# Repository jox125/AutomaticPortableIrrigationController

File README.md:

# Automatic Portable Irrigation System

This automatic watering system was developed and manufactured as my final thesis in Mechatronics at the Võru County Vocational Education Center.
In this repository you find two main parts: 
1. Water distribution system hardware overview
2. Controller software

All parts are placed in a common housing to ensure easy installation and transportation of the system.

You can find additional information in my thesis in [here](/assets/Joel_Lepp_Thesis_est.docx)

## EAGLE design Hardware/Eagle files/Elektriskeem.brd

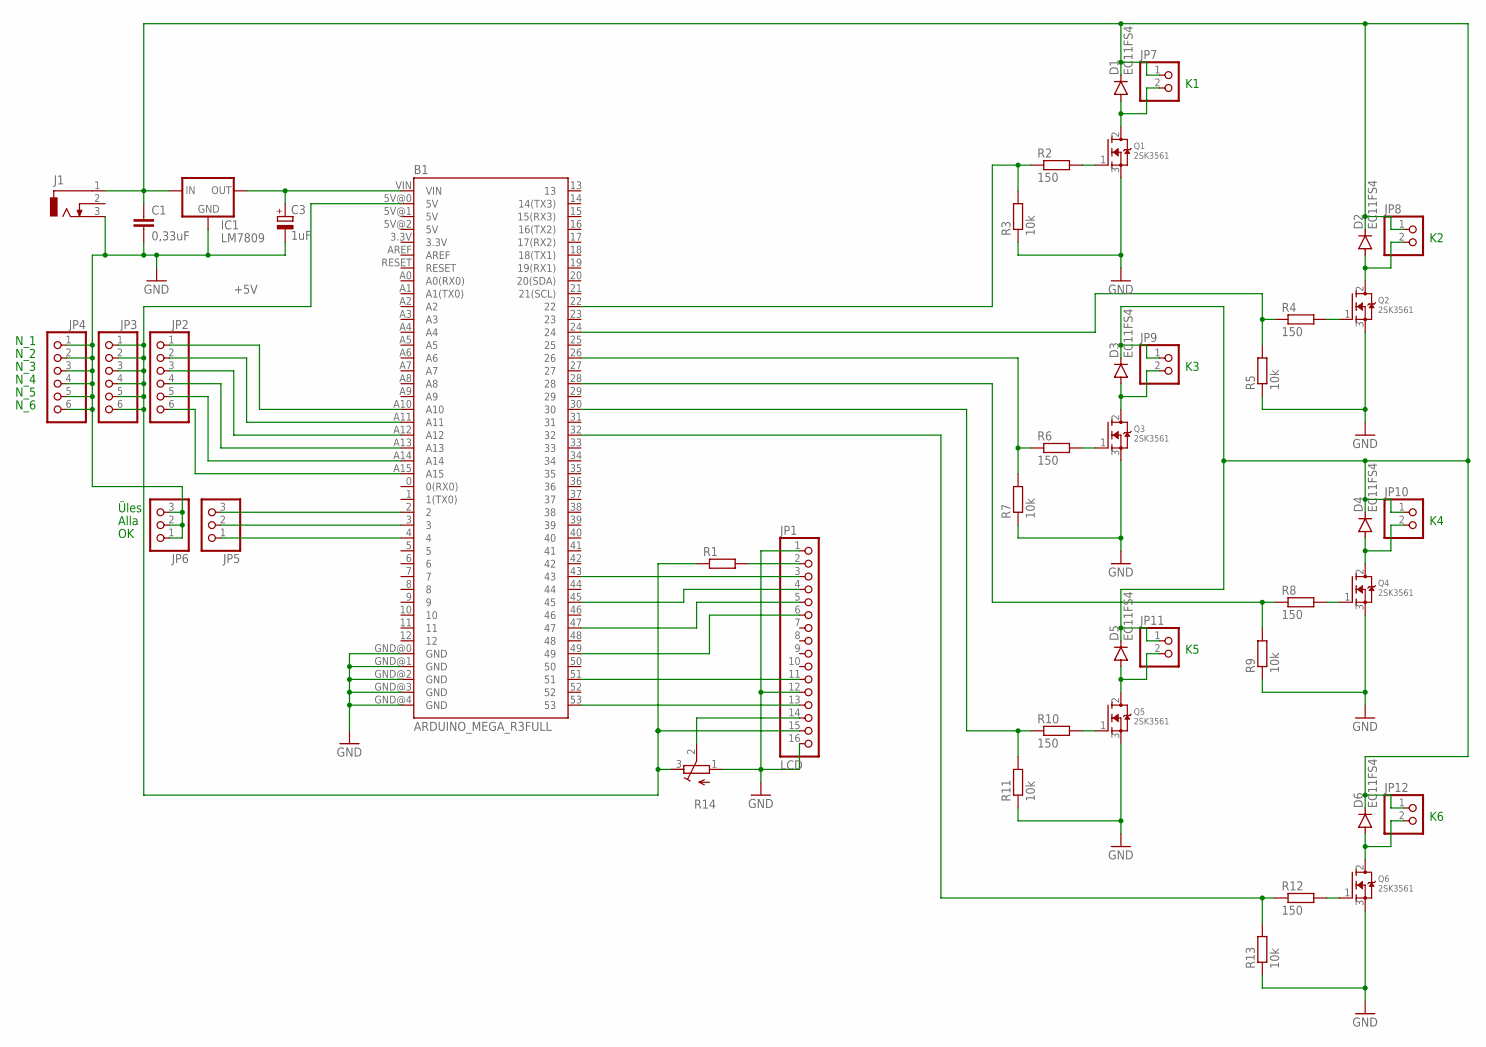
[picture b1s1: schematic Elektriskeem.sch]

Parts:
B1: ARDUINO_MEGA_R3FULL; ARDUINO_MEGA
C1: 0,33uF; C102-043X133
C3: 1uF; E2,5-6
D1, D2, D3, D4, D5, D6: EC11FS4; DO214AA
IC1: LM7809; 78XXS
J1: DCJ0303
JP1: LCD; 1X16
JP2, JP3, JP4: PINHD-1X6; 1X06
JP5, JP6: PINHD-1X3; 1X03
JP7, JP8, JP9, JP10, JP11, JP12: PINHD-1X2; 1X02
Q1, Q2, Q3, Q4, Q5, Q6: 2SK3561; TO220V
R1: R-EU_0207/12; 0207/12
R2, R4, R6, R8, R10, R12: 150; 0207/12
R3, R5, R7, R9, R11, R13: 10k; 0207/12
R14: R-TRIMM3339P; RTRIM3339P

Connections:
+5V: B1.5V@0 (5V), JP1.15, JP3.1, JP3.2, JP3.3, JP3.4, JP3.5, JP3.6, R1.1, R14.3 (E)
GND: B1.GND@0 (GND), B1.GND@1 (GND), B1.GND@2 (GND), B1.GND@3 (GND), B1.GND@4 (GND), C1.2, C3.-, IC1.GND, J1.3, JP1.1, JP1.12, JP1.16, JP4.1, JP4.2, JP4.3, JP4.4, JP4.5, JP4.6, JP6.1, JP6.2, JP6.3, Q1.3 (S), Q2.3 (S), Q3.3 (S), Q4.3 (S), Q5.3 (S), Q6.3 (S), R3.1, R5.1, R7.1, R9.1, R11.1, R13.1, R14.1 (A)
unnamed: C1.1, D1.C, D2.C, D3.C, D4.C, D5.C, D6.C, IC1.IN, J1.1, JP7.1, JP8.1, JP9.1, JP10.1, JP11.1, JP12.1
unnamed: B1.2, JP5.3
unnamed: B1.VIN, C3.+, IC1.OUT
unnamed: B1.A15, JP2.6
unnamed: B1.26, R6.1, R7.2
unnamed: B1.A14, JP2.5
unnamed: B1.A13, JP2.4
unnamed: B1.A12, JP2.3
unnamed: B1.A11, JP2.2
unnamed: B1.A10, JP2.1
unnamed: B1.43, JP1.3
unnamed: B1.53, JP1.13
unnamed: JP1.2, R1.2
unnamed: JP1.14, R14.2 (S)
unnamed: B1.51, JP1.11
unnamed: B1.45, JP1.4
unnamed: B1.47, JP1.5
unnamed: B1.49, JP1.6
unnamed: B1.3, JP5.2
unnamed: B1.4, JP5.1
unnamed: Q1.1 (G), R2.2
unnamed: D1.A, JP7.2, Q1.2 (D)
unnamed: B1.22, R2.1, R3.2
unnamed: D3.A, JP9.2, Q3.2 (D)
unnamed: Q3.1 (G), R6.2
unnamed: D5.A, JP11.2, Q5.2 (D)
unnamed: Q5.1 (G), R10.2
unnamed: B1.30, R10.1, R11.2
unnamed: D2.A, JP8.2, Q2.2 (D)
unnamed: Q2.1 (G), R4.2
unnamed: B1.24, R4.1, R5.2
unnamed: D4.A, JP10.2, Q4.2 (D)
unnamed: Q4.1 (G), R8.2
unnamed: B1.28, R8.1, R9.2
unnamed: D6.A, JP12.2, Q6.2 (D)
unnamed: Q6.1 (G), R12.2
unnamed: B1.32, R12.1, R13.2

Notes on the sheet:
Üles
Alla
N_1
N_2
N_3
N_4
N_5
N_6

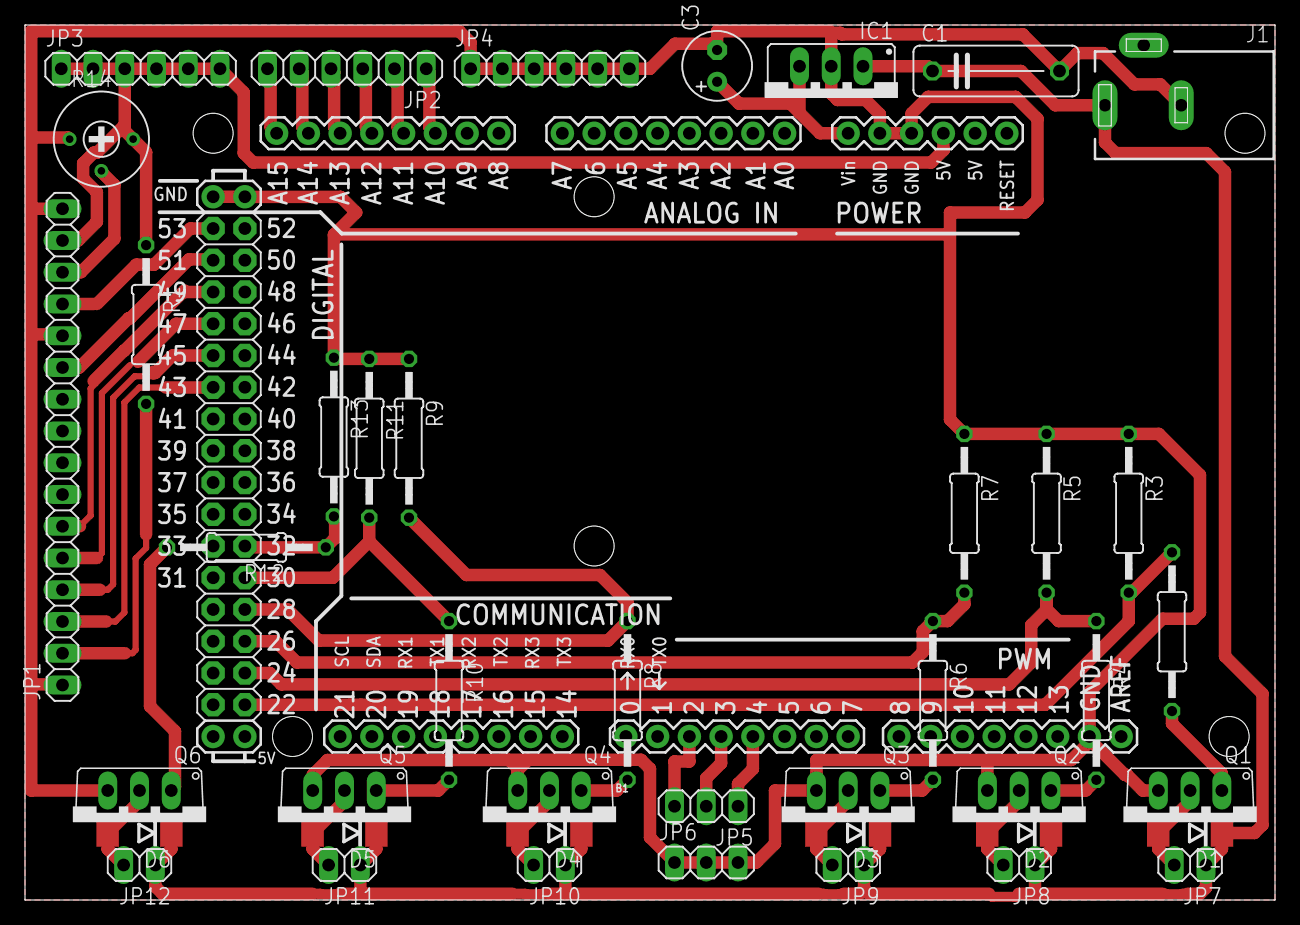
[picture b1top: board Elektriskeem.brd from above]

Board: 2 copper layers, 100.0 x 70.0 mm, 43 parts (0 on the bottom side), 39 nets.

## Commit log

2024-11-23 Created files
2024-11-23 Rename Readme Software.md to Readme.md

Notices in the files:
parts and their libraries:
SparkFun-Boards: Licensing: Creative Commons ShareAlike 4.0 International - https://creativecommons.org/licenses/by-sa/4.0
